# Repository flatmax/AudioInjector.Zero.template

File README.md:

This repo has moved to :

https://github.com/Audio-Injector/AudioInjector.zero.template

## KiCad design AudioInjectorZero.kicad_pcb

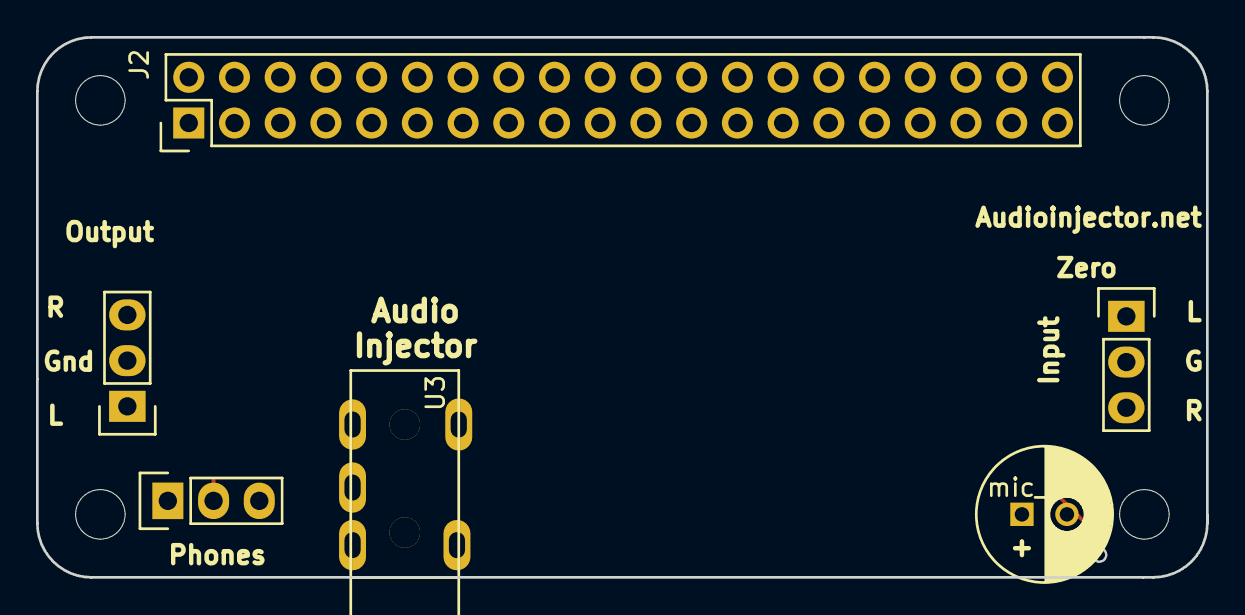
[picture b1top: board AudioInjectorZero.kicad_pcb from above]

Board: 2 copper layers, 65.0 x 30.0 mm, 10 parts (0 on the bottom side), 5 nets.

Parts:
1PIN, 1PIN#2, 1PIN#3, 1PIN#4: P***; 1pin
HP_1: OUT; Pin_Header_Straight_1x03
J2: PC104; Pin_Header_Straight_2x20
L_G_R_IN_1: OUT; Pin_Header_Straight_1x03
L_G_R_OUT_1: OUT; Pin_Header_Straight_1x03
U3: pj313
mic_1: Mic; C_Radial_D7.5_L11.2_P2.5

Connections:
/Codec/Ring: HP_1.3, U3.2
/Codec/Tip: HP_1.1, U3.3
AGND: HP_1.2, L_G_R_IN_1.2, L_G_R_OUT_1.2, U3.1, mic_1.2
DGND: J2.6, J2.9, J2.14, J2.20, J2.25, J2.30, J2.34, J2.39
V5: J2.2, J2.4

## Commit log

2017-11-09 Board template for mounting measurements.
2017-11-09 Added the gerbers.
2018-01-11 moved to flatmax2
